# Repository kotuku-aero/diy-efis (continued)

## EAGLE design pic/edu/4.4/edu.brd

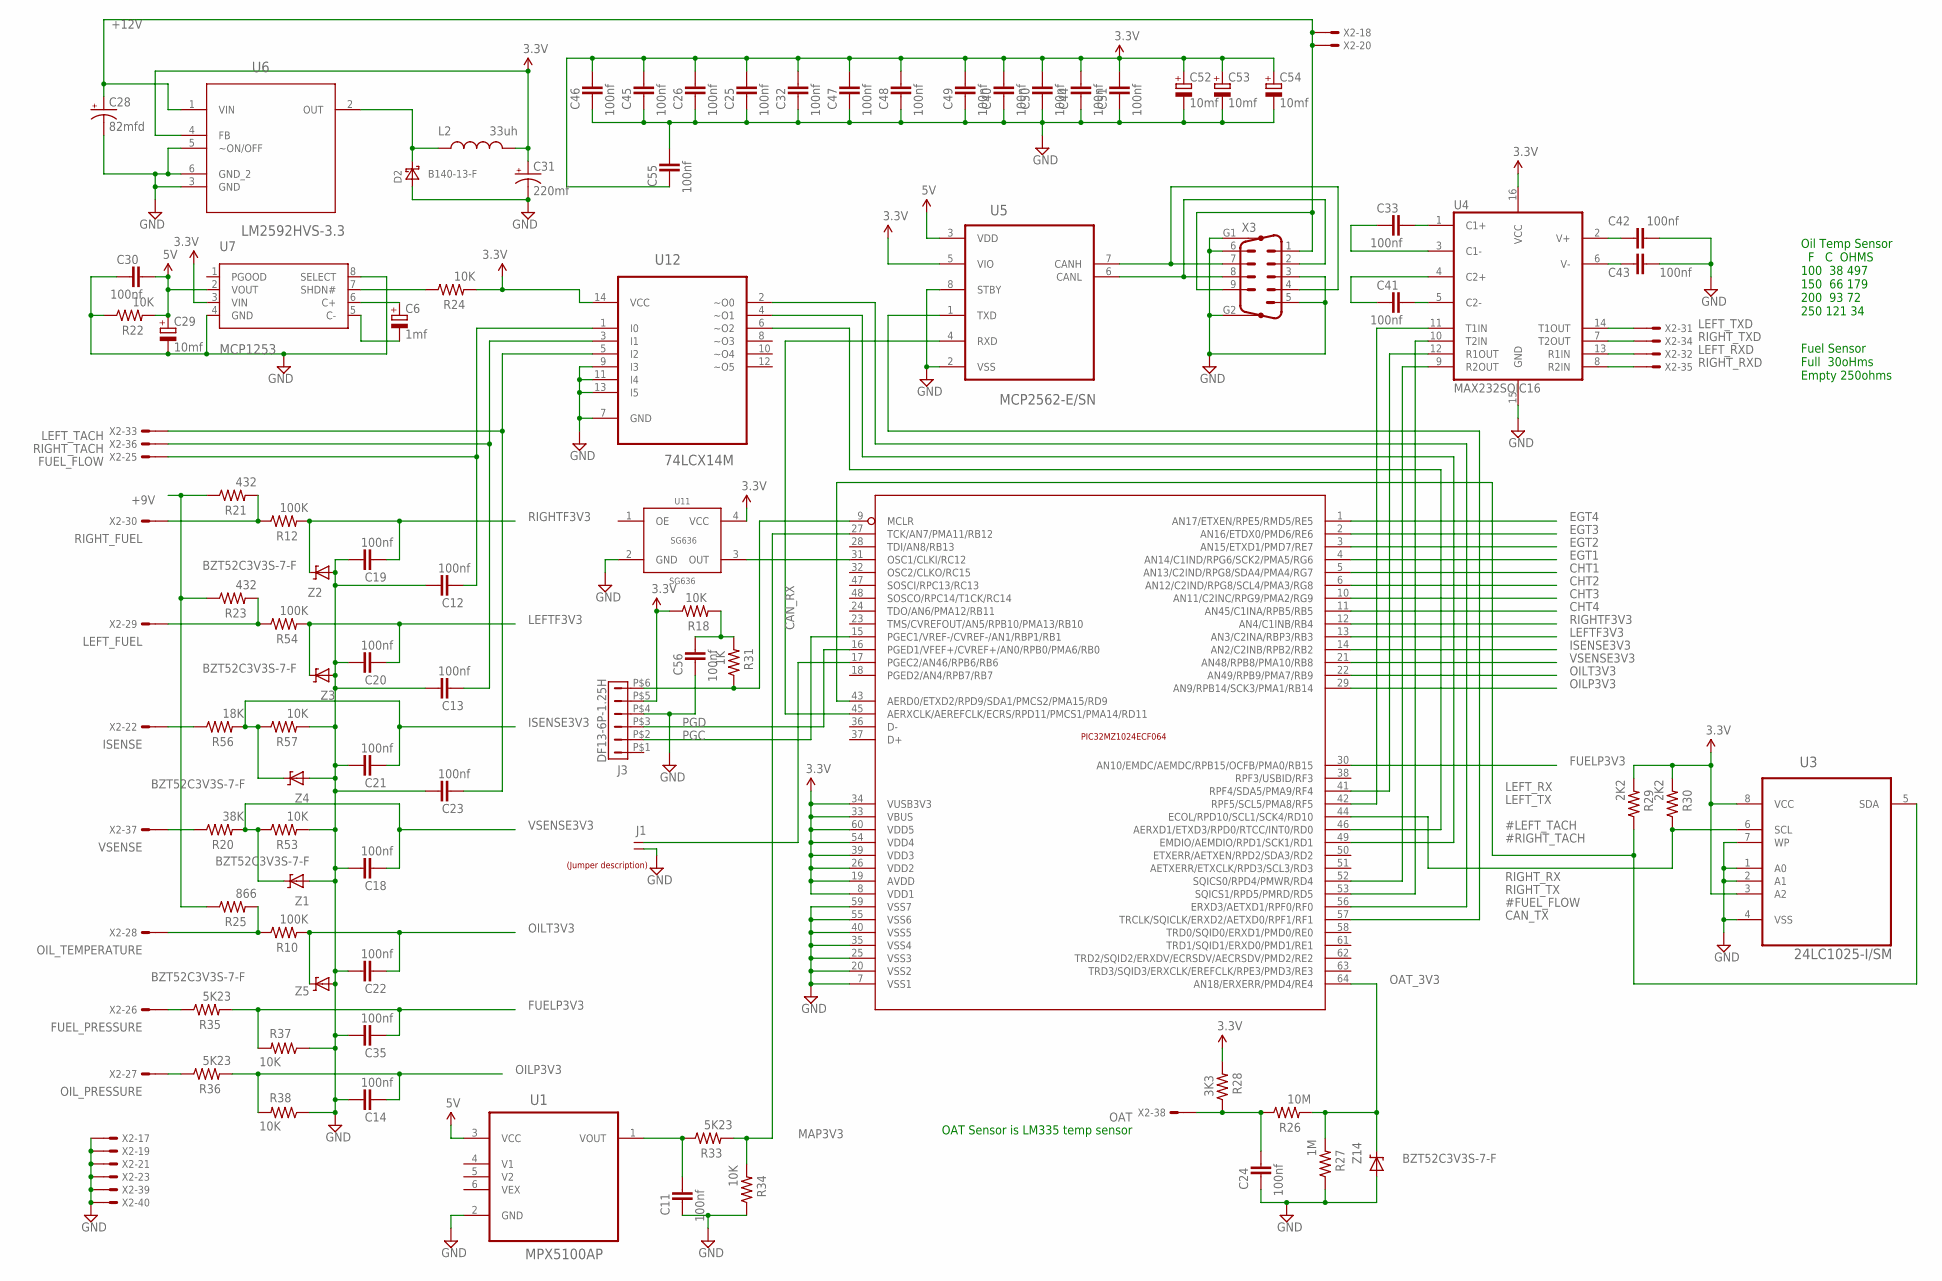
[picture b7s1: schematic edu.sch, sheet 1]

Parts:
C6: 1mf; SMC_A; PARTNO F931C105MAA
C11, C12, C13, C14, C18, C19, C20, C21, C22, C23, C24, C25, C26, C30, C32, C33, C35, C40, C41, C42, C43, C44, C45, C46, C47, C48, C49, C50, C51, C55, C56: 100nf; C805; PARTNO CL21F104ZBCNNNC
C28: 82mfd; SVPF-E7
C29, C52, C53, C54: 10mf; SMC_A; PARTNO T491A106K004AT
C31: 220mf; EIA7343; PARTNO T545X227M016ATE035
D2: B140-13-F; SMA; PARTNO B140-13-F
J1: M20-9770246; JUMPER-1X2; PARTNO M20-9770246
J3: DF13-6P-1.25H; DF13A-6P-1.25H; PARTNO DF13A-6P-1.25H(20)
L2: 33uh; 1812; PARTNO LQH43MN330K03L
R10, R12, R54: 100K; 0603-RES; PARTNO RC0603FR-07100KL
R18, R22, R24, R34, R37, R38, R53, R57: 10K; 0603-RES; PARTNO RC0603FR-0710KL
R20: 38K; 0603-RES; PARTNO RC0603FR-0738K3L
R21, R23: 432; 0603-RES; PARTNO RC0603FR-07432RL
R25: 866; 0603-RES; PARTNO RC0603FR-07866RL
R26: 10M; 0603-RES; PARTNO RC0603FR-075K23L
R27: 1M; 0603-RES; PARTNO RC0603FR-0710KL
R28: 3K3; 0603-RES; PARTNO RC0603FR-0710KL
R29, R30: 2K2; 0603-RES; PARTNO RC0603FR-072K2L
R31: 1K; 0603-RES; PARTNO RC0603FR-0710KL
R33, R35, R36: 5K23; 0603-RES; PARTNO RC0603FR-075K23L
R56: 18K; 0603-RES; PARTNO RC0603FR-0718KL
U1: MPX5100AP; FREESCALE_CASE_867B-04
U3: 24LC1025-I/SM; SOIC8-N_MC; PARTNO 24LC1025-I/P
U4: MAX232SOIC16; SO016; PARTNO MAX3232ECDR
U5: MCP2562-E/SN; SOIC-8N; PARTNO MCP2562-E/SN
U6: LM2592HVS-3.3; TO170P1435X457-5N; PARTNO LM2592HVSX-3.3/NOPB
U7: MCP1253; MSOP8; PARTNO MCP1253-33X50I/MS
U11: SG636; PARTNO SG-636PCE 10.000MHZ
U12: 74LCX14M; SOIC127P600X175-14N; PARTNO 74LCX14MX
U$2: PIC32MZ1024; TQFP-64
U$5: LABEL_JUMPER_1X2; JUMP2_DESC
X2: 057-040-1; PARTNO SBH11-PBPC-D20-ST-BK
X3: M09HP
Z1, Z2, Z3, Z4, Z5, Z14: BZT52C3V3S-7-F; SOD-323; PARTNO BZT52C3V3S-7-F

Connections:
3.3V: C25.1, C26.1, C31.A (+), C32.1, C40.1, C44.1, C45.1, C46.1, C47.1, C48.1, C49.1, C50.1, C51.1, C52.+, C53.+, C54.+, C55.2, J3.P$5 (5), L2.2, R18.1, R24.2, R28.2, R29.2, R30.2, U3.3 (A2), U3.8 (VCC), U4.16 (VCC), U5.5 (VIO), U6.4 (FB), U7.3 (VIN), U11.4 (VCC), U12.14 (VCC), U$2.8 (VDD1), U$2.19 (AVDD), U$2.26 (VDD2), U$2.33 (VBUS), U$2.34 (VUSB3V3), U$2.39 (VDD3), U$2.54 (VDD4), U$2.60 (VDD5)
5V: C29.+, C30.1, R22.2, U1.3 (VCC), U5.3 (VDD), U7.2 (VOUT)
!MCLR: J3.P$6 (6), R31.1, U$2.9 (MCLR)
#FUEL_FLOW: U12.2 (~O0), U$2.56 (ERXD3/AETXD1/RPF0/RF0)
#LEFT_TACH: U12.6 (~O2), U$2.46 (AERXD1/ETXD3/RPD0/RTCC/INT0/RD0)
#RIGHT_TACH: U12.4 (~O1), U$2.49 (EMDIO/AEMDIO/RPD1/SCK1/RD1)
+9V: R21.1, R23.1, R25.1; also elsewhere on the board
+12V: C28.P$2 (+), U6.1 (VIN), X2.18, X2.20, X3.1, X3.9; also elsewhere on the board
CANH: U5.7 (CANH), X3.4, X3.7
CANL: U5.6 (CANL), X3.2, X3.8
CAN_RX: U5.4 (RXD), U$2.45 (AERXCLK/AEREFCLK/ECRS/RPD11/PMCS1/PMA14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)
CAN_TX: U5.1 (TXD), U$2.57 (TRCLK/SQICLK/ERXD2/AETXD0/RPF1/RF1)
CHT1: U$2.5 (AN13/C2IND/RPG8/SDA4/PMA4/RG7); also elsewhere on the board
CHT2: U$2.6 (AN12/C2IND/RPG8/SCL4/PMA3/RG8); also elsewhere on the board
CHT3: U$2.10 (AN11/C2INC/RPG9/PMA2/RG9); also elsewhere on the board
CHT4: U$2.11 (AN45/C1INA/RPB5/RB5); also elsewhere on the board
EGT1: U$2.4 (AN14/C1IND/RPG6/SCK2/PMA5/RG6); also elsewhere on the board
EGT2: U$2.3 (AN15/ETXD1/PMD7/RE7); also elsewhere on the board
EGT3: U$2.2 (AN16/ETDX0/PMD6/RE6); also elsewhere on the board
EGT4: U$2.1 (AN17/ETXEN/RPE5/RMD5/RE5); also elsewhere on the board
FUELP3V3: C35.2, R35.2, R37.2, U$2.30 (AN10/EMDC/AEMDC/RPB15/OCFB/PMA0/RB15)
FUEL_FLOW: C12.2, U12.1 (I0), X2.25
FUEL_PRESSURE: R35.1, X2.26
GND: C11.2, C12.1, C13.1, C14.1, C18.1, C19.1, C20.1, C21.1, C22.1, C23.1, C24.2, C25.2, C26.2, C28.P$1 (-), C29.-, C30.2, C31.C (-), C32.2, C35.1, C40.2, C42.1, C43.1, C44.2, C45.2, C46.2, C47.2, C48.2, C49.2, C50.2, C51.2, C52.-, C53.-, C54.-, C55.1, C56.2, D2.A, J1.2, J3.P$4 (4), R22.1, R27.1, R34.1, R37.1, R38.1, R53.2, R57.2, U1.2 (GND), U3.1 (A0), U3.2 (A1), U3.4 (VSS), U3.7 (WP), U4.15 (GND), U5.2 (VSS), U5.8 (STBY), U6.3 (GND), U6.5 (~ON/OFF), U6.6 (GND_2), U7.4 (GND), U7.8 (SELECT), U11.2 (GND), U12.7 (GND), U12.9 (I3), U12.11 (I4), U12.13 (I5), U$2.7 (VSS1), U$2.20 (VSS2), U$2.25 (VSS3), U$2.35 (VSS4), U$2.40 (VSS5), U$2.55 (VSS6), U$2.59 (VSS7), X2.17, X2.19, X2.21, X2.23, X2.39, X2.40, X3.3, X3.5, X3.6, X3.G1, X3.G2, Z1.2 (A), Z2.2 (A), Z3.2 (A), Z4.2 (A), Z5.2 (A), Z14.2 (A); also elsewhere on the board
ISENSE: R56.1, X2.22
ISENSE3V3: C21.2, R56.2, R57.1, U$2.14 (AN2/C2INB/RPB2/RB2), Z4.1 (C)
LEFTF3V3: C20.2, R54.2, U$2.13 (AN3/C2INA/RBP3/RB3), Z3.1 (C)
LEFT_FUEL: R23.2, R54.1, X2.29
LEFT_RX: U4.12 (R1OUT), U$2.41 (RPF4/SDA5/PMA9/RF4)
LEFT_RXD: U4.13 (R1IN), X2.32
LEFT_TACH: C23.2, U12.5 (I2), X2.33
LEFT_TX: U4.11 (T1IN), U$2.42 (RPF5/SCL5/PMA8/RF5)
LEFT_TXD: U4.14 (T1OUT), X2.31
MAP3V3: R33.2, R34.2, U$2.27 (TCK/AN7/PMA11/RB12)
unnamed: C56.1, R18.2, R31.2
unnamed: R24.1, U7.7 (SHDN#)
unnamed: C33.1, U4.1 (C1+)
unnamed: C33.2, U4.3 (C1-)
unnamed: C41.2, U4.4 (C2+)
unnamed: C41.1, U4.5 (C2-)
unnamed: C42.2, U4.2 (V+)
unnamed: C43.2, U4.6 (V-)
unnamed: D2.C, L2.1, U6.2 (OUT)
unnamed: U11.3 (OUT), U$2.31 (OSC1/CLKI/RC12)
unnamed: J1.1, U$2.17 (PGEC2/AN46/RPB6/RB6)
unnamed: C6.-, U7.5 (C-)
unnamed: C6.+, U7.6 (C+)
unnamed: C11.1, R33.1, U1.1 (VOUT)
OAT: C24.1, R26.1, R28.1, X2.38
OAT_3V3: R26.2, R27.2, U$2.64 (AN18/ERXERR/PMD4/RE4), Z14.1 (C)
OILP3V3: C14.2, R36.2, R38.2, U$2.29 (AN9/RPB14/SCK3/PMA1/RB14)
OILT3V3: C22.2, R10.2, U$2.22 (AN49/RPB9/PMA7/RB9), Z5.1 (C)
OIL_PRESSURE: R36.1, X2.27
OIL_TEMPERATURE: R10.1, R25.2, X2.28
PGC: J3.P$2 (2), U$2.15 (PGEC1/VREF-/CVREF-/AN1/RBP1/RB1)
PGD: J3.P$3 (3), U$2.16 (PGED1/VFEF+/CVREF+/AN0/RPB0/PMA6/RB0)
RIGHTF3V3: C19.2, R12.2, U$2.12 (AN4/C1INB/RB4), Z2.1 (C)
RIGHT_FUEL: R12.1, R21.2, X2.30
RIGHT_RX: U4.9 (R2OUT), U$2.52 (SQICS0/RPD4/PMWR/RD4)
RIGHT_RXD: U4.8 (R2IN), X2.35
RIGHT_TACH: C13.2, U12.3 (I1), X2.36
RIGHT_TX: U4.10 (T2IN), U$2.53 (SQICS1/RPD5/PMRD/RD5)
RIGHT_TXD: U4.7 (T2OUT), X2.34
SCL: R30.1, U3.6 (SCL), U$2.44 (ECOL/RPD10/SCL1/SCK4/RD10)
SDA: R29.1, U3.5 (SDA), U$2.43 (AERD0/ETXD2/RPD9/SDA1/PMCS2/PMA15/RD9)
VSENSE: R20.1, X2.37
VSENSE3V3: C18.2, R20.2, R53.1, U$2.21 (AN48/RPB8/PMA10/RB8), Z1.1 (C)

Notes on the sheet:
Oil Temp Sensor F C OHMS 100 38 497 150 66 179 200 93 72 250 121 34
Fuel Sensor Full 30oHms Empty 250ohms
OAT Sensor is LM335 temp sensor

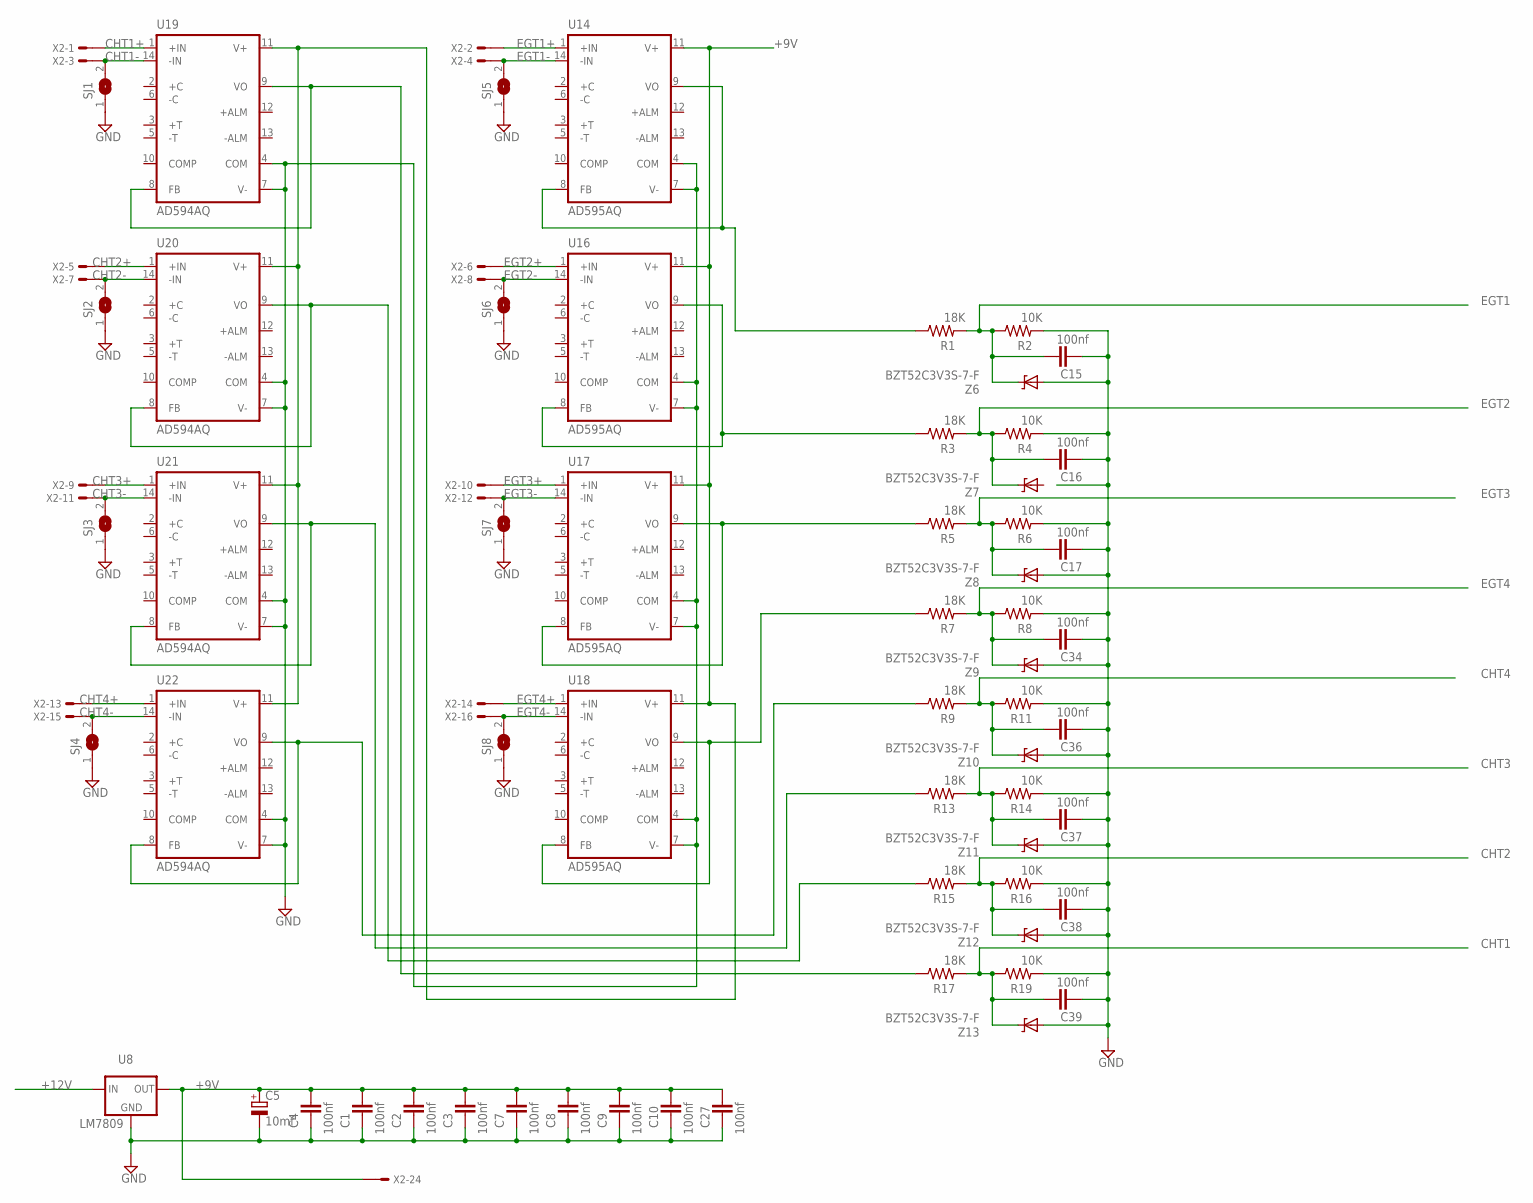
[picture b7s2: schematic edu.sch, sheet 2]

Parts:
C1, C2, C3, C4, C7, C8, C9, C10, C15, C16, C17, C27, C34, C36, C37, C38, C39: 100nf; C805; PARTNO CL21F104ZBCNNNC
C5: 10mf; SMC_A; PARTNO CL31A106KAHNNNE
R1, R3, R5, R7, R9, R13, R15, R17: 18K; 0603-RES; PARTNO RC0603FR-0718KL
R2, R4, R6, R8, R11, R14, R16, R19: 10K; 0603-RES; PARTNO RC0603FR-0710KL
SJ1, SJ2, SJ3, SJ4, SJ5, SJ6, SJ7, SJ8: SOLDERJUMPERCLOSED; SOLDERJUMPER_CLOSEDWIRE
U8: LM7809; 78XXS; PARTNO LM7808CT
U14, U16, U17, U18: AD595AQ; DIL14
U19, U20, U21, U22: AD594AQ; DIL14
X2: 057-040-1; PARTNO SBH11-PBPC-D20-ST-BK
Z6, Z7, Z8, Z9, Z10, Z11, Z12, Z13: BZT52C3V3S-7-F; SOD-323; PARTNO BZT52C3V3S-7-F

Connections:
+9V: C1.1, C2.1, C3.1, C4.1, C5.+, C7.1, C8.1, C9.1, C10.1, C27.1, U8.OUT, U14.11 (V+), U16.11 (V+), U17.11 (V+), U18.11 (V+), U19.11 (V+), U20.11 (V+), U21.11 (V+), U22.11 (V+), X2.24; also elsewhere on the board
+12V: U8.IN; also elsewhere on the board
CHT1: C39.1, R17.2, R19.1, Z13.1 (C); also elsewhere on the board
CHT1+: U19.1 (+IN), X2.1
CHT1-: SJ1.2, U19.14 (-IN), X2.3
CHT2: C38.1, R15.2, R16.1, Z12.1 (C); also elsewhere on the board
CHT2+: U20.1 (+IN), X2.5
CHT2-: SJ2.2, U20.14 (-IN), X2.7
CHT3: C37.1, R13.2, R14.1, Z11.1 (C); also elsewhere on the board
CHT3+: U21.1 (+IN), X2.9
CHT3-: SJ3.2, U21.14 (-IN), X2.11
CHT4: C36.1, R9.2, R11.1, Z10.1 (C); also elsewhere on the board
CHT4+: U22.1 (+IN), X2.13
CHT4-: SJ4.2, U22.14 (-IN), X2.15
EGT1: C15.1, R1.2, R2.1, Z6.1 (C); also elsewhere on the board
EGT1+: U14.1 (+IN), X2.2
EGT1-: SJ5.2, U14.14 (-IN), X2.4
EGT2: C16.1, R3.2, R4.1, Z7.1 (C); also elsewhere on the board
EGT2+: U16.1 (+IN), X2.6
EGT2-: SJ6.2, U16.14 (-IN), X2.8
EGT3: C17.1, R5.2, R6.1, Z8.1 (C); also elsewhere on the board
EGT3+: U17.1 (+IN), X2.10
EGT3-: SJ7.2, U17.14 (-IN), X2.12
EGT4: C34.1, R7.2, R8.1, Z9.1 (C); also elsewhere on the board
EGT4+: U18.1 (+IN), X2.14
EGT4-: SJ8.2, U18.14 (-IN), X2.16
GND: C1.2, C2.2, C3.2, C4.2, C5.-, C7.2, C8.2, C9.2, C10.2, C15.2, C16.2, C17.2, C27.2, C34.2, C36.2, C37.2, C38.2, C39.2, R2.2, R4.2, R6.2, R8.2, R11.2, R14.2, R16.2, R19.2, SJ1.1, SJ2.1, SJ3.1, SJ4.1, SJ5.1, SJ6.1, SJ7.1, SJ8.1, U8.GND, U14.4 (COM), U14.7 (V-), U16.4 (COM), U16.7 (V-), U17.4 (COM), U17.7 (V-), U18.4 (COM), U18.7 (V-), U19.4 (COM), U19.7 (V-), U20.4 (COM), U20.7 (V-), U21.4 (COM), U21.7 (V-), U22.4 (COM), U22.7 (V-), Z6.2 (A), Z8.2 (A), Z9.2 (A), Z10.2 (A), Z11.2 (A), Z12.2 (A), Z13.2 (A); also elsewhere on the board
unnamed: R7.1, U18.8 (FB), U18.9 (VO)
unnamed: R1.1, U14.8 (FB), U14.9 (VO)
unnamed: R3.1, U16.8 (FB), U16.9 (VO)
unnamed: R5.1, U17.8 (FB), U17.9 (VO)
unnamed: R17.1, U19.8 (FB), U19.9 (VO)
unnamed: R9.1, U22.8 (FB), U22.9 (VO)
unnamed: R13.1, U21.8 (FB), U21.9 (VO)
unnamed: R15.1, U20.8 (FB), U20.9 (VO)

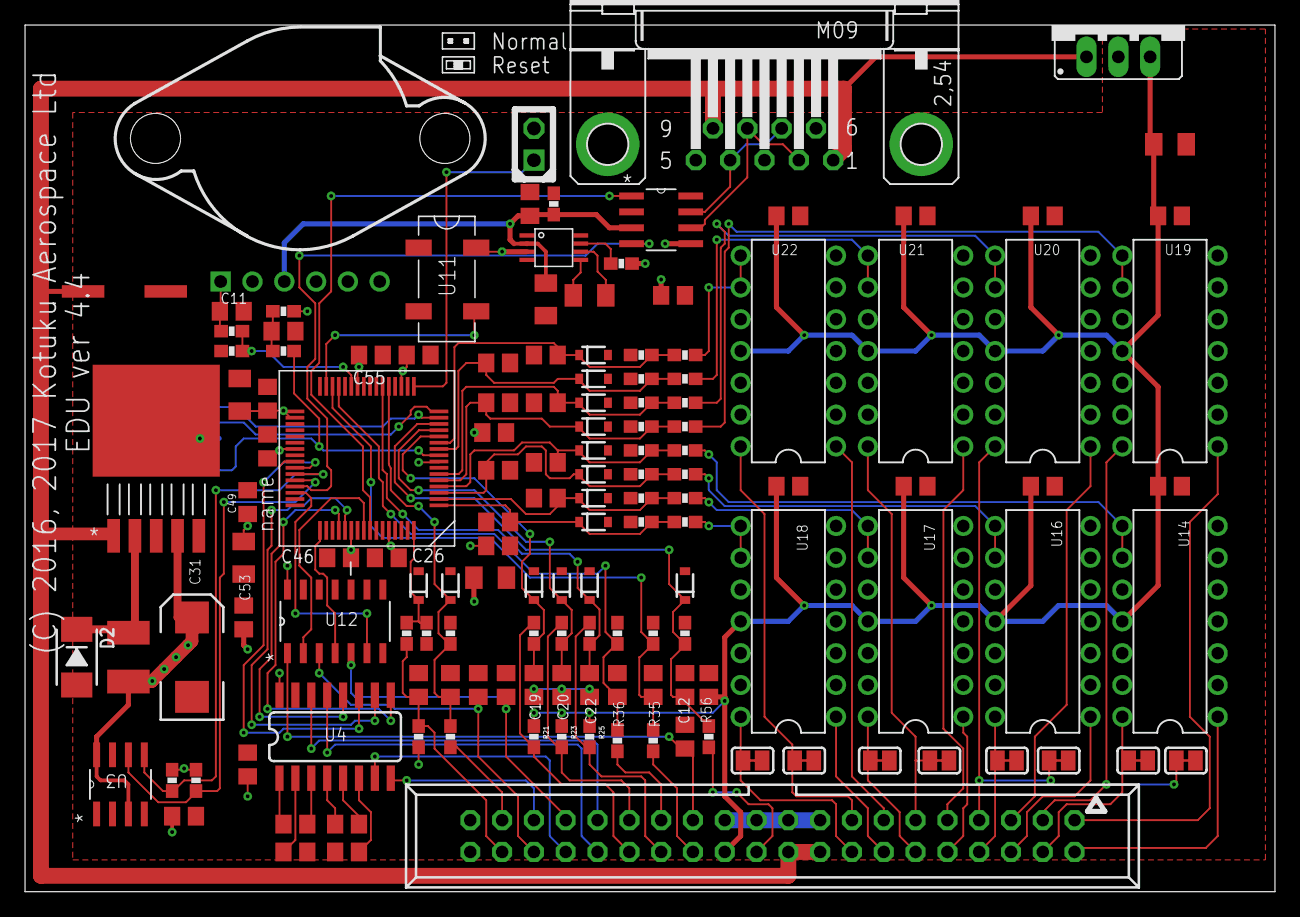
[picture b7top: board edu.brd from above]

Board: 2 copper layers, 99.8 x 69.2 mm, 144 parts (1 on the bottom side), 91 nets.

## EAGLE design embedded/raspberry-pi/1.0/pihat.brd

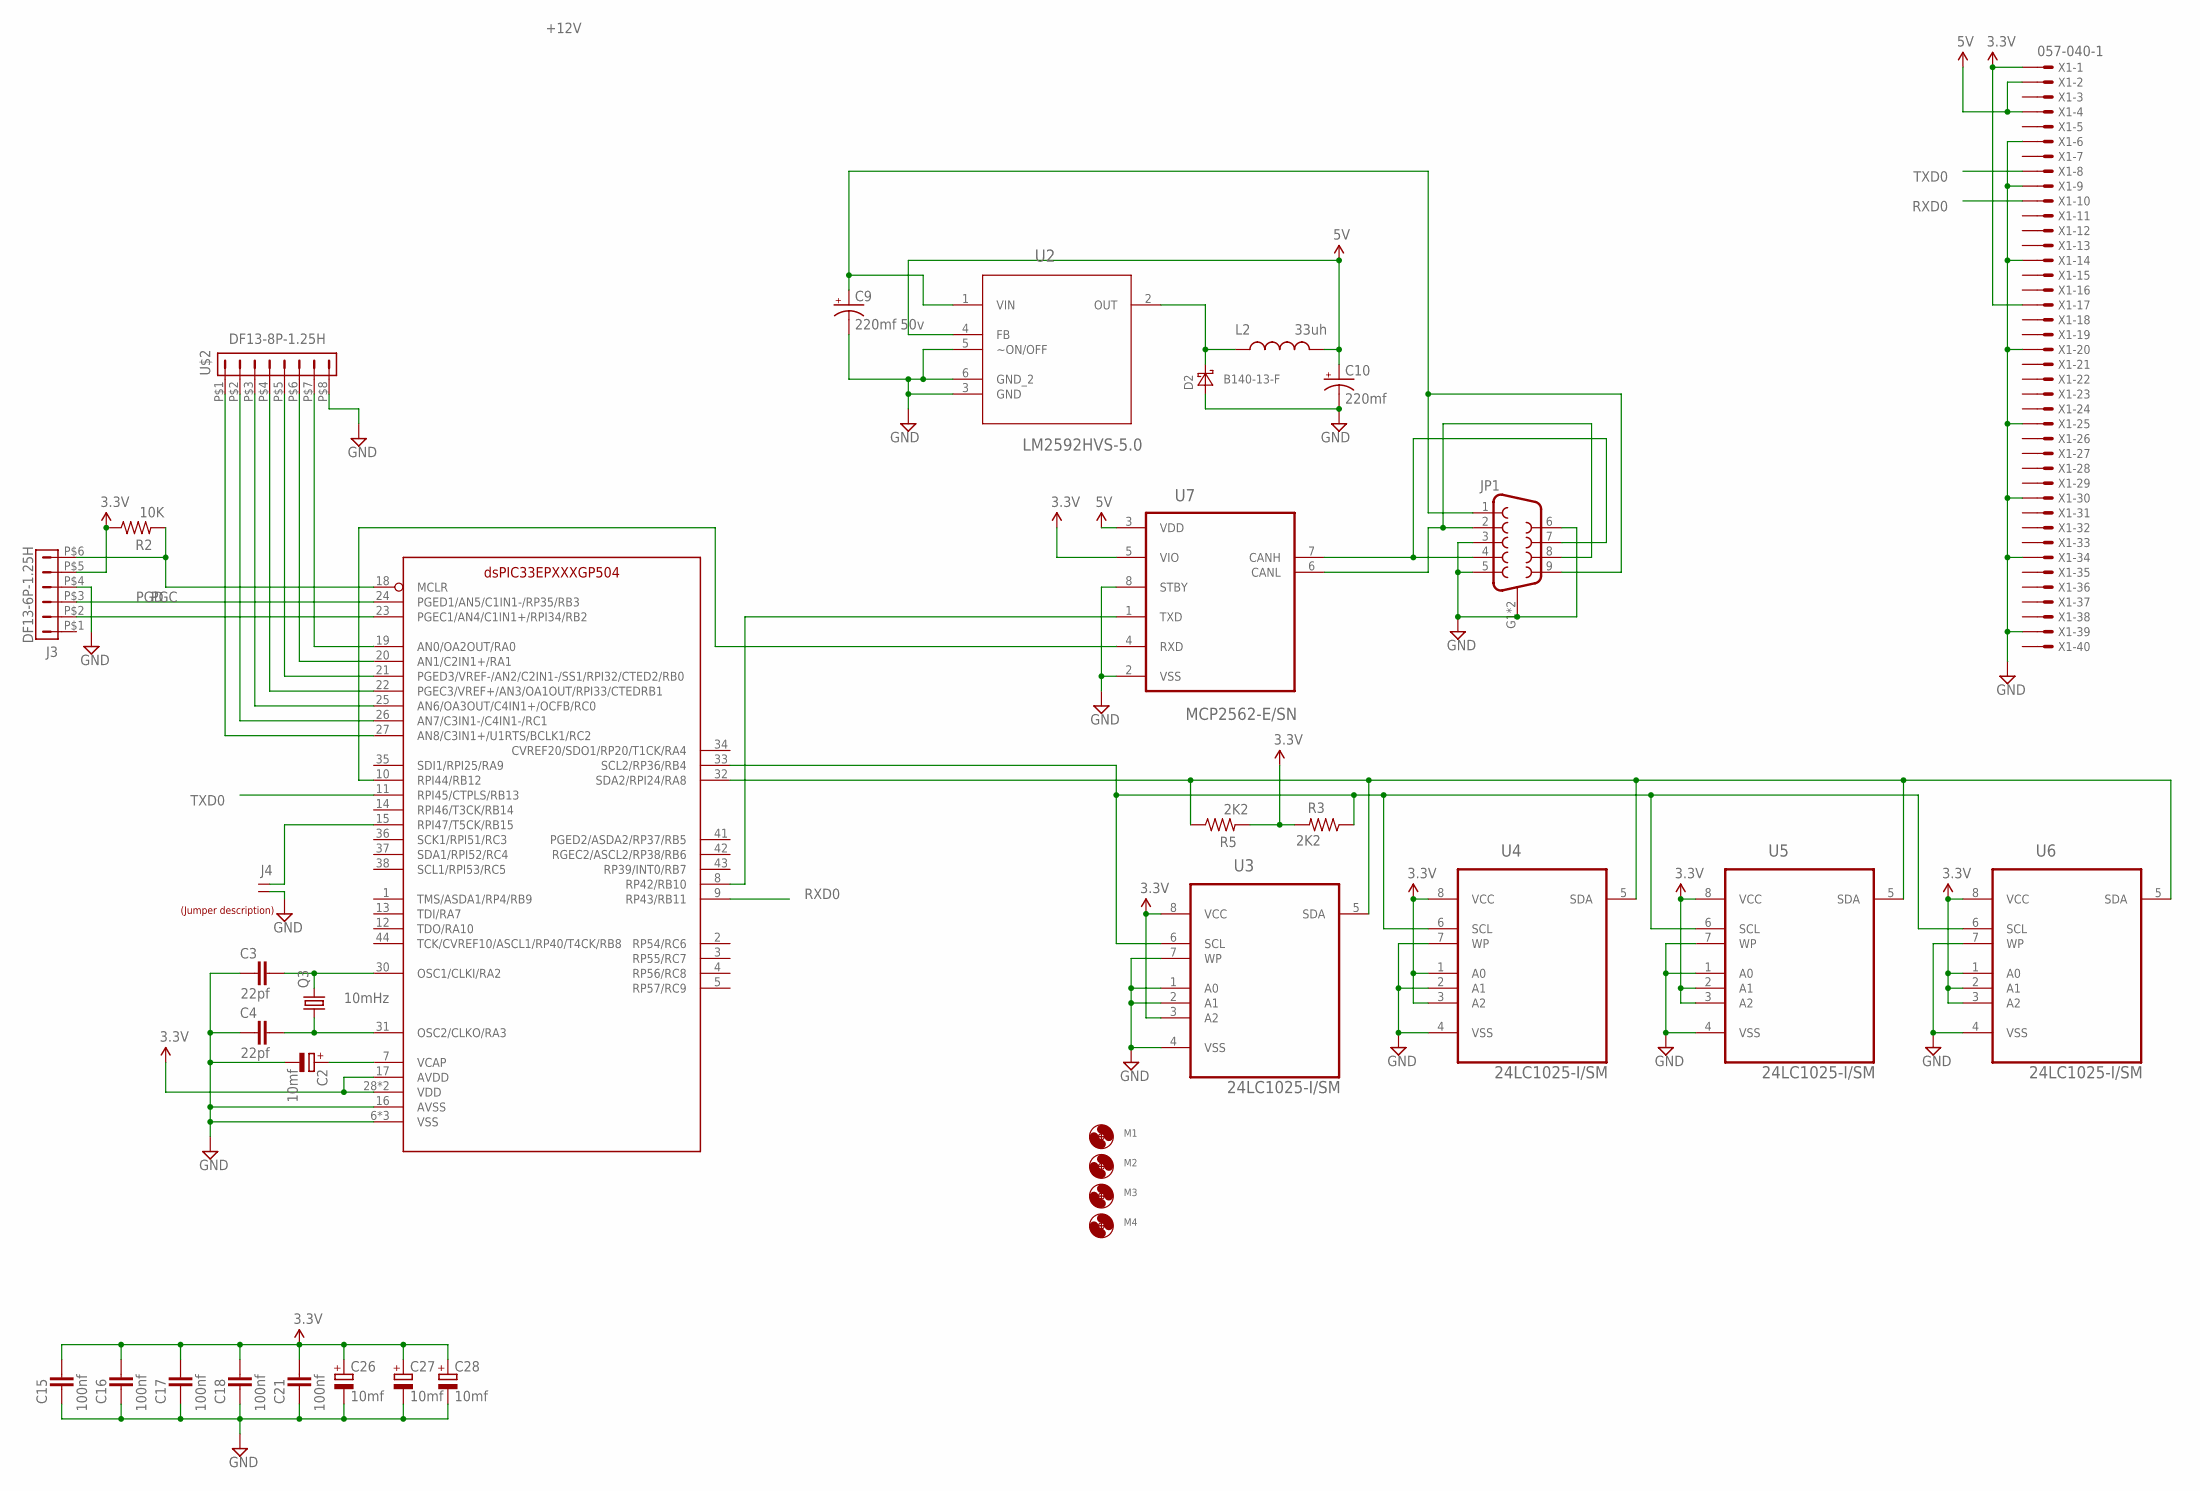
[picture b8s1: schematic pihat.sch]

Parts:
C2, C26, C27, C28: 10mf; SMC_A; PARTNO T491A106K004AT
C3, C4: 22pf; C805; PARTNO C0805C220J5GACTU
C9: 220mf 50v; EIA7343; PARTNO T545X227M016ATE035
C10: 220mf; EIA7343; PARTNO T545X227M016ATE035
C15, C16, C17, C18, C21: 100nf; C805; PARTNO CL21F104ZBCNNNC
D2: B140-13-F; SMA; PARTNO B140-13-F
J3: DF13-6P-1.25H; DF13A-6P-1.25H; PARTNO DF13A-6P-1.25H(20)
J4: JUMPER-1X2; PARTNO M20-9770246
JP1: DB9MALE; DB9_MALE; PARTNO 5747840-3
L2: 33uh; 1812; PARTNO B78108S1333K
M1, M2, M3, M4: MOUNT-HOLE2.8; 2,8
Q3: 10mHz; HC49/S; PARTNO ATS100B-E
R2: 10K; 0603-RES; PARTNO RC0603FR-0710KL
R3, R5: 2K2; 0603-RES; PARTNO RC0603FR-072K2L
U1: DSPIC33EPXXXGP504; TQFP44; PARTNO DSPIC33EP512GP504-I/PT
U2: LM2592HVS-5.0; TO170P1435X457-5N; PARTNO LM2592HVSX-5.0/NOPB
U3, U4, U5, U6: 24LC1025-I/SM; SOIC8-N_MC; PARTNO 24LC1025T-I/SN
U7: MCP2562-E/SN; SOIC-8N; PARTNO MCP2562-E/SN
U$1: LABEL_JUMPER_1X2; JUMP2_DESC
U$2: DF13-8P-1.25H; DF13A-8P-1.25H; PARTNO DF13-8P-1.25H(50)
X1: 057-040-1

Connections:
3.3V: C15.1, C16.1, C17.1, C18.1, C21.1, C26.+, C27.+, C28.+, J3.P$5 (5), R2.1, R3.2, R5.2, U1.17 (AVDD), U1.28 (VDD), U1.40 (VDD), U3.3 (A2), U3.8 (VCC), U4.1 (A0), U4.3 (A2), U4.8 (VCC), U5.2 (A1), U5.3 (A2), U5.8 (VCC), U6.1 (A0), U6.2 (A1), U6.3 (A2), U6.8 (VCC), U7.5 (VIO), X1.1, X1.17
5V: C10.A (+), L2.2, U2.4 (FB), U7.3 (VDD), X1.2, X1.4
!MCLR: J3.P$6 (6), R2.2, U1.18 (MCLR)
+12V: C9.A (+), JP1.1, JP1.9, U2.1 (VIN)
CANH: JP1.4, JP1.7, U7.7 (CANH)
CANL: JP1.2, JP1.8, U7.6 (CANL)
GND: C2.-, C3.2, C4.2, C9.C (-), C10.C (-), C15.2, C16.2, C17.2, C18.2, C21.2, C26.-, C27.-, C28.-, D2.A, J3.P$4 (4), J4.2, JP1.3, JP1.5, JP1.6, JP1.G1 (SHIELD), JP1.G2 (SHIELD), U1.6 (VSS), U1.16 (AVSS), U1.29 (VSS), U1.39 (VSS), U2.3 (GND), U2.5 (~ON/OFF), U2.6 (GND_2), U3.1 (A0), U3.2 (A1), U3.4 (VSS), U3.7 (WP), U4.2 (A1), U4.4 (VSS), U4.7 (WP), U5.1 (A0), U5.4 (VSS), U5.7 (WP), U6.4 (VSS), U6.7 (WP), U7.2 (VSS), U7.8 (STBY), U$2.P$8 (8), X1.6, X1.9, X1.14, X1.20, X1.25, X1.30, X1.34, X1.39
unnamed: U1.19 (AN0/OA2OUT/RA0), U$2.P$7 (7)
unnamed: U1.20 (AN1/C2IN1+/RA1), U$2.P$6 (6)
unnamed: U1.21 (PGED3/VREF-/AN2/C2IN1-/SS1/RPI32/CTED2/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), U$2.P$5 (5)
unnamed: U1.22 (PGEC3/VREF+/AN3/OA1OUT/RPI33/CTEDRB1), U$2.P$4 (4)
unnamed: U1.25 (AN6/OA3OUT/C4IN1+/OCFB/RC0), U$2.P$3 (3)
unnamed: U1.26 (AN7/C3IN1-/C4IN1-/RC1), U$2.P$2 (2)
unnamed: U1.27 (AN8/C3IN1+/U1RTS/BCLK1/RC2), U$2.P$1 (1)
unnamed: D2.C, L2.1, U2.2 (OUT)
unnamed: C3.1, Q3.2, U1.30 (OSC1/CLKI/RA2)
unnamed: U1.10 (RPI44/RB12), U7.4 (RXD)
unnamed: C2.+, U1.7 (VCAP)
unnamed: U1.8 (RP42/RB10), U7.1 (TXD)
unnamed: C4.1, Q3.1, U1.31 (OSC2/CLKO/RA3)
PGC: J3.P$2 (2), U1.23 (PGEC1/AN4/C1IN1+/RPI34/RB2)
PGD: J3.P$3 (3), U1.24 (PGED1/AN5/C1IN1-/RP35/RB3)
RESET#: J4.1, U1.15 (RPI47/T5CK/RB15)
RXD0: U1.9 (RP43/RB11), X1.10
SCL: R3.1, U1.33 (SCL2/RP36/RB4), U3.6 (SCL), U4.6 (SCL), U5.6 (SCL), U6.6 (SCL)
SDA: R5.1, U1.32 (SDA2/RPI24/RA8), U3.5 (SDA), U4.5 (SDA), U5.5 (SDA), U6.5 (SDA)
TXD0: U1.11 (RPI45/CTPLS/RB13), X1.8

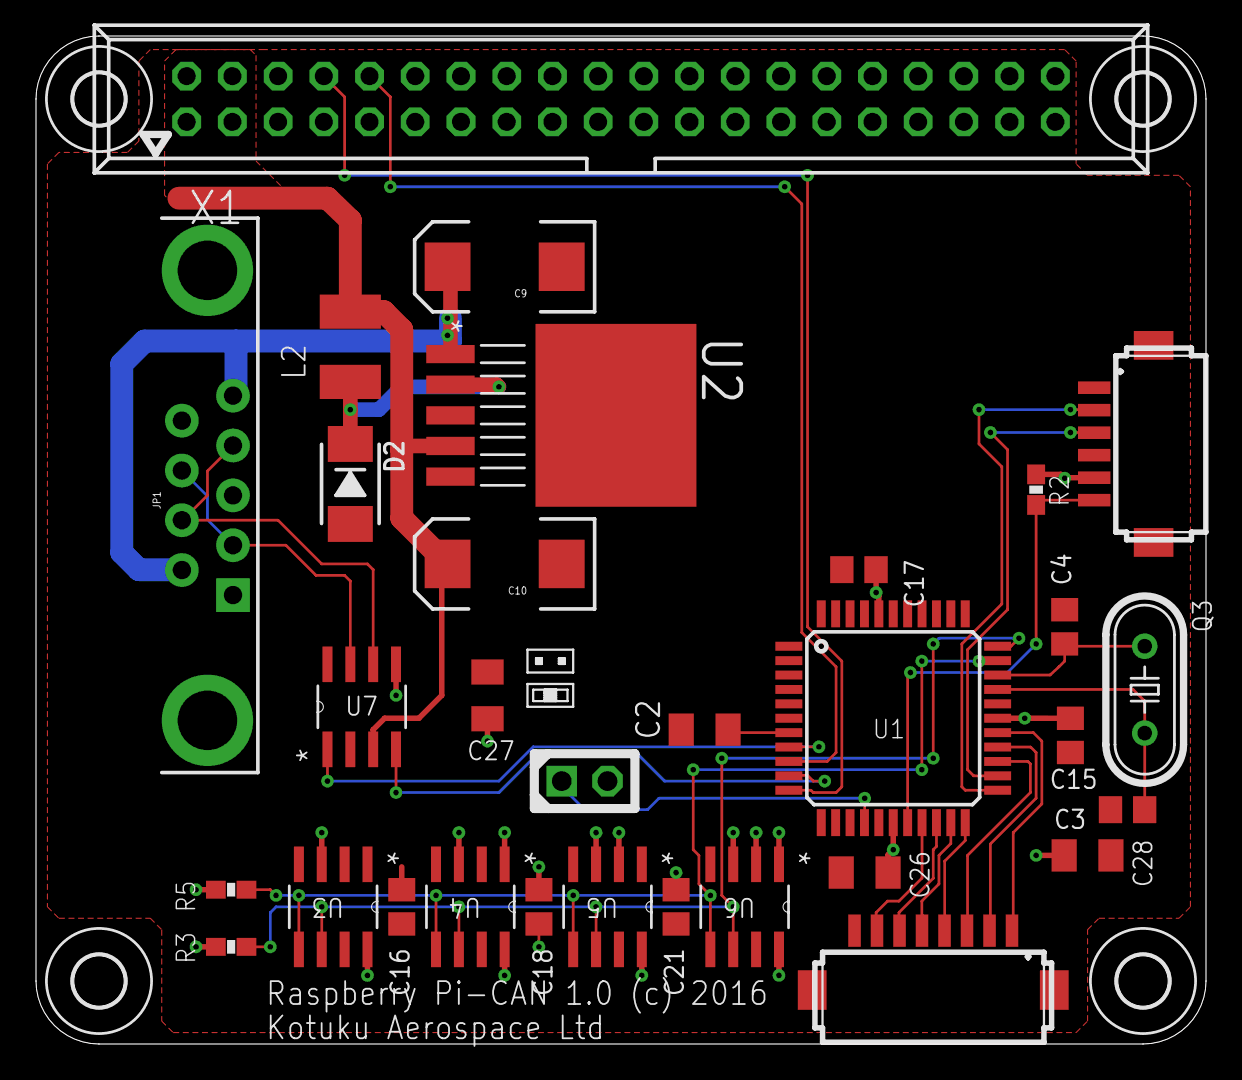
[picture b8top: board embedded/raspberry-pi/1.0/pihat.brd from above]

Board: 2 copper layers, 65.0 x 56.0 mm, 36 parts (0 on the bottom side), 27 nets.

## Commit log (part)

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2016-07-18 Added merged tree to project
2016-07-20 Fixed build for Windows
2016-07-20 Updated build for X11 client
2016-07-21 Fixed x11 build
2016-07-21 Fixed runtime issues on x11, Fixed errors on serial can due to bugs in dspic
2016-07-21 Added pi setup for demo
2016-07-21 Updated build for EDU, basic functions working ok. Port to new dspic33EP code Aplha1
2016-08-11 Update README.md
    Added more of a description as to the project, also called for volunteers.
2016-12-14 Tidy up build and made application use native types
2016-12-14 Updated with a working win32-efis build
2017-01-26 Updated with new design
2017-02-06 Updated build to make simplere and comply with pi spec
2017-07-16 Added latest mechanicals
2017-07-18 Added missing DWG files
2017-09-06 Removed projects from pre-2017 release
2017-09-06 Added Electron support library for Linux Added Neutron library
2017-09-06 Shared files from kotuku. Still many libraries to document and push
2017-09-06 Added muon to the release
2017-09-06 Added ion scripting library
2017-09-15 Added reference designs with the 2016 code. This will be refactored to use the 2017 implementation and removed as it is tested.
2017-09-15 Added proton library
2017-09-15 Updated helpers
2017-09-17 Updated tool chain
2017-09-17 Updated build to include splash.c
2017-09-17 Updated routines
2017-10-05 Work on photon ECMA script bindings Built for kotuku embedded products
2017-10-06 More work on implementing widgets in ECMA script
2017-10-08 Aded screen shot for docs
2017-10-16 Minor bug fixes and code readability updates
2017-10-27 Minor change to code to stop calling routine twice
2017-10-29 Added proton cli
2017-11-03 Worked on tidying up cli commands for embedded devices
2017-11-10 Fixed concurrency issues in registry code
2017-11-16 Added functionality to allow paste from clipboard on windows Fixed can_aerspace bug where long strings were not sent correctly from the CLI
2017-11-17 Work in progress on bug with the cli_string functions
2017-11-17 Added missing files
2017-11-19 Removed dependency on buggy string library and made use std c libraries. Needs work on runtime size though. For now just more stress testing
2017-11-19 Fixed numeric parse errors
2017-11-19 Added example attitude cfg that is in test
2017-11-27 Removed old font engine and replace with simpler version
2017-11-27 Added manifest file support
2017-11-27 Updated manifest decoder
2017-11-28 Re created proxy code
2017-12-05 Added truetype reader and rasterizer
2017-12-05 Update to runnable version
2017-12-06 Started converting built in windows to support events and javascript hooks
2017-12-06 Added base64 encoded splash screen in readiness for converting bitmap code to PNG decoder
2017-12-07 Added PNG decoder
2017-12-08 Have built a version of the png decoder
2017-12-12 Work on hauffman decompressor
2017-12-13 Fixed decompress bugs added pixel cache to speed up decompressor
2017-12-14 Fixed decode bugs in the png decompressor
2017-12-14 Updated logo and splash screen
2017-12-14 Updated with splash screen
2017-12-14 Trying to get markdown to work!
2017-12-14 Updated on_paint signature and README.md
2017-12-14 Fixed code to correctly pass keys to widgets
2017-12-15 Work on getting fonts working
2017-12-19 Updated work on font decoder
2017-12-19 Font engine changed to use polygon code. Not very good rendering at present but it is functional.
2017-12-20 Fixed font caching code
2017-12-20 Work on tesellation of curves
2017-12-22 Work on polygon code
2017-12-27 Work on anti-alias code for font engine
2017-12-31 Added font generator code. Removed ttf as too expensive for an embedded system Still support fonts as files.
2017-12-31 Removed deprecated files
2018-01-01 Fixed font code and generator Fixed polypolygon code to handle anti-clockwise polygons Added neo font as built in font.
2018-01-01 Removed define
2018-01-02 Code review identified too much use of anonymous void * as arguments, changed to type specific pointers
2018-01-07 Fixed paint bugs
2018-01-07 Comm Device changes
2018-01-08 Fixed bugs with signatures of callbacks
2018-01-08 Updated build for embedded solution
2018-01-09 Fixed minor bugs
2018-01-10 Updated font tool to handle bold, italic fonts and add any pixel size
2018-01-11 Added some code to make coercion easier
2018-01-15 Fixed naming on library functions
2018-01-17 Fixed build with new registration options
2018-01-17 Work on integrating ion with photon
2018-01-17 Project updates
2018-01-17 Added routines to the widget code
2018-01-17 Fixed property functions for photon
2018-01-18 Have basic JS widget working
2018-01-19 Added some helper routines for the Kotuku embedded products Fixed functions to render using JS
2018-01-19 Added code for more JS functions
2018-01-19 Added on_create and on_close messages
2018-01-19 Fixed issue where id_create not sent to js handlers
2018-01-22 Added gluon floating point library as embedded systems need a more deterministic library
2018-01-22 Added embedded build files
2018-01-22 Removed libm implementation as found issue elsewhere
2018-01-24 Minor changes to make sure initial splash screen bitmap is always rendered onto a 32bit framebuffer
2018-01-26 Updated with work on menu system Added support for F1-F9 to be used to simulate hardware keys
2018-01-26 Fixed drawing bugs
2018-01-28 Menu work
2018-01-29 Added script to allow JS to be added to projects
2018-01-30 Bug fixes
2018-02-04 Added tests
2018-02-06 Work on embedded JS code
2018-02-06 Added basic unit test framework
2018-02-09 Fixed minor bug where embedded systems could not run ion
2018-02-09 Fix bug when no alarms defined on a published value
2018-02-09 Embedded testing
2018-02-11 Work on embedded stack size
2018-03-05 work on publisher
2018-03-12 Fixing bugs in publisher
2018-03-13 Added gluon library which is the data logger
2018-03-14 Work on implementing a data logger command line interface
2018-03-22 Added code to handle monitored datapoints. Needed for kotuku AHRS
2018-03-23 Updates to publisher
2018-03-27 Work in progress
2018-03-28 Added pi build for vs2017
2018-03-30 Moved files
2018-04-11 work on 12c code
2018-04-20 Work on PI version
2018-07-14 Restore missing files
2018-07-14 Added project files
2018-07-14 Fixed path issues
2018-07-14 moved projects around
2018-07-14 Added ignore to the repository
2018-07-14 Fixed library versions
2018-07-14 Fixed path problem
2018-07-14 Fixed project paths and ignore more binary files
2018-07-15 Build changes when connected to a PI
2018-07-15 Fixed compile errors
2018-07-16 Getting menu system working again
2018-07-18 Resolvd event routing issues
2018-07-19 Changed layout of events
2018-08-04 work on i2c version
2018-11-04 Work on CLI Add helper routine to the publisher
2018-11-04 Work on the EDU init code
2019-05-11 Added simpler generic interface than PIHAT
2019-07-25 Added presentation to tree
2019-07-31 Fixed link to presentation
2020-10-11 Remove stale projects
2020-10-11 Remove tcw files
2020-10-21 Fixed build on linux for msh
2020-10-22 Added support for ch45-49
2020-12-28 Restored krypton.h, getopt.h Sorted startup signature for msh Updated to latest windows 10 sdk
2020-12-29 Marge kotuku WIP into project
2020-12-29 Kotuku v@ changes
2020-12-29 Added id spreadsheet
2020-12-29 Added image so wiki works
2020-12-30 Update on removing old code
2021-01-02 Added clr handlers
2021-01-04 All basic files are added, does not build yet. Committing to keep changes.
2021-01-04 Removed un-necessary nano files for use on CanFly
2021-01-05 Tidy projects
2021-01-06 Photon compiled
2021-01-06 ION compiles
2021-01-07 Finally compiling MSH
2021-01-07 Implemented basic filesystem to allow loading assemblies using msh
2021-01-09 Added docs
2021-01-09 Work on conversions
2021-01-10 Moved events to the widget
2021-01-14 Moved core lib to project
2021-01-17 Clean up runtime
2021-01-18 Compiling with static jump table
2021-01-18 Moved nano into ion project
2021-01-18 Link errors sorted
2021-01-19 Sorted out msg callbacks
2021-01-23 Removed un-used old projects
2021-01-23 Remove old files no longer buildable
2021-01-23 Remove project not relevant any more
2021-01-23 Removed unused project
2021-01-25 Not running with debugger yet, just saving major refactoring
2021-01-27 Simplify framework to use canfly threads
2021-03-04 work on the framework
2021-03-08 Tidy up of CLR code
2021-03-09 Fixing minor issues
2021-03-13 Sorting some bugs
2021-03-14 Added new assemblies
2021-03-14 Added MSH
2021-03-24 Building metadata processor for CanFly
2021-03-30 Removed old files
2021-03-30 Change to build structure. WIP
2021-03-30 Start of CMake build support
2021-03-30 Make files for all targets
2021-03-30 Added doc
2021-03-31 WIP on moving to vscode
2021-04-02 Work on Makefile build
2021-04-02 Makefile for Proton
2021-04-02 Have metadata processor working as part of the build
2021-04-05 Fixed structure of libraries
2021-04-07 Emitter for debug information is completed
2021-04-07 Ignore build folders
2021-04-07 Added missing binaries
2021-04-07 Made paths in assembly consistent with vscode debugger
2021-04-07 Fixed statement processor
2021-04-09 Added debugging information to the processor
2021-04-09 Moved canflymsg as a base type and simplify code
2021-04-10 Fixed types
2021-04-11 Update on web forms
2021-04-12 Work on debugger and code tidy
2021-04-13 Changed debug structure
2021-04-14 Fixed scope debug info
2021-04-14 Updates to runtime system
2021-04-14 Tidy up project
2021-04-14 Remove duplicated binary
2021-04-15 Work on configs
2021-04-15 Restore font generator that converts ttf fonts to CanFly fixed bitmap fonts
2021-04-16 Fixed bug with gauge widget
2021-04-16 Moved emulator
2021-04-16 Work on extension
2021-04-18 Added missing
2021-04-19 Moved tools to correct spot
2021-04-19 Updated vsix to latest
2021-04-19 Added picture for README
2021-04-19 Updated vsix for testing
2021-04-19 Explain more about running the tools
2021-04-20 Added code to make the vsix console work
2021-04-20 Minor fixes
2021-04-20 Added pic
2021-04-20 Added doc images
2021-04-20 Fixed build errors
2021-04-21 Fixed path startup
2021-04-21 updated vsix
2021-04-21 Updated makefiles
2021-04-22 Update build
2021-05-03 Added Regex from the nanoFramework fixed issue. Still testing the regex code
2021-05-04 Work on code completion
2021-05-04 UpdateDialGauge
2021-05-06 Re structure menu widget
2021-05-07 Remove vulnerability
2021-05-08 Update on widgets to make more like C#
2021-05-11 Work on render engine
2021-05-12 Latest interpreter
2021-05-12 Fixed minor bugs in system
2021-05-12 Fixed inter not running as release build
2021-05-15 Added koutku app's
2021-05-19 MSBuild
2021-09-22 Bump nth-check from 2.0.0 to 2.0.1 in /tools/vscode
    Bumps [nth-check](https://github.com/fb55/nth-check) from 2.0.0 to 2.0.1.
    - [Release notes](https://github.com/fb55/nth-check/releases)
    - [Commits](https://github.com/fb55/nth-check/compare/v2.0.0...v2.0.1)
    ---
    updated-dependencies:
    - dependency-name: nth-check
2023-06-23 2023 merge head
2023-07-24 Fixed build and missing files
2024-01-28 Merge Kotuku build into diy-efis
    This is a major update that includes the first cut of a moving map display as well as Yehudi that generates layouts from xml definitions
2024-01-28 Added PFD project
2024-01-28 Build of new interfaces
2024-02-13 Change tool link
2024-02-14 Update description of other projects
2024-02-14 More docs
2024-02-15 Tidy up of paths
2024-07-18 update to canfly
2024-07-18 Reversed bug
2026-03-13 Remove old version, now on REL01 branch
2026-03-14 Updated emulation library
2026-03-14 Minor updates to api files to decrease changes from timestamp only
2026-03-14 Fix bug in enumeration of flightplans
2026-03-15 Tidy up of upstream code
2026-03-15 Commander starting to get there
2026-03-16 Minor updates
2026-03-25 Update types to a more sensible representation
2026-04-25 Fix bug in canfly types
2026-04-30 Update definitions to simplify kmag
2026-05-07 Fixed kmag_annunciator
2026-05-24 Ignore temp generated artifacts
2026-05-24 Fix signature for map code
2026-05-24 Sort annunciator
2026-05-25 Work on map and api code
2026-05-26 Work on map
2026-05-27 work on canvas
2026-05-27 Map widget
2026-06-09 Work on spatial databases
2026-06-09 Updated API types
2026-06-27 Update with correct flag
2026-06-27 Work on samples
2026-06-28 Latest canfly lib
2026-06-28 Updated to handle custom build scripts
2026-06-29 Work on runtime debugger
